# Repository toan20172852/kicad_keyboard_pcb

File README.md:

# PCB Design_Keyboard 4 button
## Goal Project
1...

## Reference
https://github.com/ruiqimao/keyboard-pcb-guide

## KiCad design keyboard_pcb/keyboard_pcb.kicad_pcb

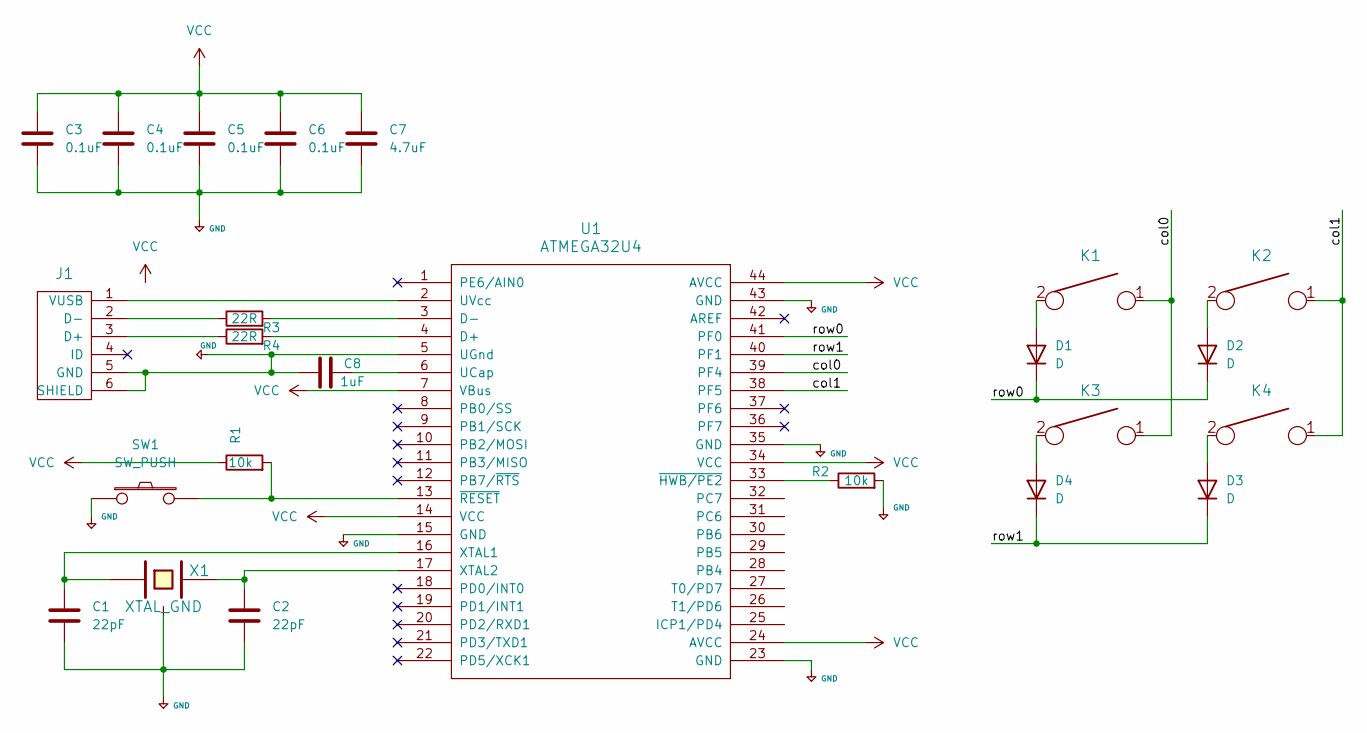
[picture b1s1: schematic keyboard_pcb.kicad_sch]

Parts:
C1, C2: 22pF; C_0805_2012Metric_Pad1.18x1.45mm_HandSolder
C3, C4, C5, C6: 0.1uF; C_0805_2012Metric_Pad1.18x1.45mm_HandSolder
C7: 4.7uF; C_0805_2012Metric_Pad1.18x1.45mm_HandSolder
C8: 1uF; C_0805_2012Metric_Pad1.18x1.45mm_HandSolder
D1, D2, D3, D4: D; D_SOD123_axial
J1: USB_mini_micro_B; USB_miniB_hirose_5S8
K1, K2, K3, K4: KEYSW; Mx_Alps_100
R1, R2: 10k; R_0805_2012Metric_Pad1.20x1.40mm_HandSolder
R3, R4: 22R; R_0805_2012Metric_Pad1.20x1.40mm_HandSolder
SW1: SW_PUSH; SW_SPST_TL3342
U1: ATMEGA32U4; LQFP-44_10x10mm_P0.8mm
X1: XTAL_GND; Crystal_SMD_3225-4Pin_3.2x2.5mm_HandSoldering

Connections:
+5V: C1.2, C2.2, C3.2, C4.2, C5.2, C6.2, C7.2, C8.1, J1.5 (GND), J1.6 (SHIELD), R2.2, SW1.1, U1.5 (UGnd), U1.15 (GND), U1.23 (GND), U1.35 (GND), U1.43 (GND), X1.3
/col0: K1.1, K3.1, U1.39 (PF4)
/col1: K2.1, K4.1, U1.38 (PF5)
/row0: D1.1 (K), D2.1 (K), U1.41 (PF0)
/row1: D3.1 (K), D4.1 (K), U1.40 (PF1)
unnamed: D1.2 (A), K1.2
unnamed: D2.2 (A), K2.2
unnamed: D3.2 (A), K4.2
unnamed: D4.2 (A), K3.2
unnamed: J1.3 (D+), R4.1
unnamed: J1.2 (D-), R3.1
unnamed: J1.1 (VUSB), U1.2 (UVcc)
unnamed: R4.2, U1.4 (D+)
unnamed: R3.2, U1.3 (D-)
unnamed: C8.2, U1.6 (UCap)
unnamed: C1.1, U1.16 (XTAL1), X1.1
unnamed: C2.1, U1.17 (XTAL2), X1.2
unnamed: R2.1, U1.33 (~HWB/PE2)
unnamed: R1.2, SW1.2, U1.13 (~RESET)
VCC: C3.1, C4.1, C5.1, C6.1, C7.1, R1.1, U1.7 (VBus), U1.14 (VCC), U1.24 (AVCC), U1.34 (VCC), U1.44 (AVCC)

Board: 2 copper layers, 24 parts (0 on the bottom side), 20 nets, no tracks yet.

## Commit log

2023-08-10 Added Resistor to Schematic
2023-08-11 Added Lib for Project
2023-08-11 Schematic Completed, PCB drawing
2023-08-11 Modify Contents
